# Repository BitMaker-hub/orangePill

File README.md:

# The Orange Pill
## Description
The OrangePill is a new social mechanism to onboard, gift, transfer or sell bitcoin in a physical, safe and reusable way.

It is a real HW Orange Pill that can be used in a community as cash. It also can be the entry point for those who doesn't know anything about Bitcoin and the best, it can be used as many times you want. 

## ATTENTION! This project is still in developement and must be tested on tesnet

## How can I use it?
Receive 💊 ➡️ Create 🌱💦 ➡️ Save ₿ 🔐➡️ Give it away

Receive 🔐 💊 ➡️ Unlock 🌱 ₿ ➡️ Reboot 💊 ➡️ Repeat with others 🔄

## How it works?
### PILL AS A KEYBOARD
The OrangePill works as a input HID device, it emulates keyboard strokes. Every time you push it's button sends keystrokes.
It don't need any specific app to work. Works on any device or pc, you just need to open a notepad or any text editor and press the pill button.

Posible inputs:

- One push:   Shows current status, display options and show xpub or mnemonic depending of it's state.
- Two pushes: Shows # times pill was used, public gpg of interal hw + signed message.
- Hold 5 sec: Depending of it's state > Start seed generation / Unlock seed / Reset pill
- SHAKE: During seed generation or seed unlock.

##PILL STATES

The orangePill has currently three sates.

VIRGIN: No seed present. Needs to generate entropy. 
LOCKED: Seed present. When you make one push you can only see xpub.
UNLOCKED: Seed revealed. When you make one push you can see mnemonic.

## HW Specifictions
- ESP32S2
- LEDs WS2812B
- Button
- Accelerometer KXTJ3-1057
- ATTEC608A

## Libraires
- Main library -> <a href="https://www.arduino.cc/reference/en/libraries/ubitcoin/">uBitcoin</a>
- Adafruit_NeoPixel
- kxtj3-1057
- hidkeyboard

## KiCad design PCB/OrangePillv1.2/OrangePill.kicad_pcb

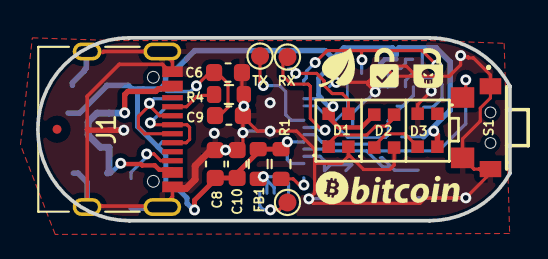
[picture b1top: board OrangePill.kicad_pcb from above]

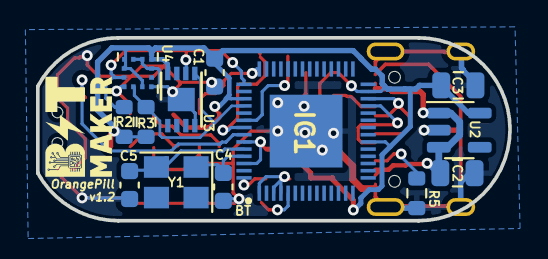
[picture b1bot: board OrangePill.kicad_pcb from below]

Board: 2 copper layers, 26.2 x 10.2 mm, 29 parts (13 on the bottom side), 20 nets.

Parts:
BT1: BOOT; TestPoint_Pad_D1.0mm
C1, C9, C10: 0.1uF; C_0603_1608Metric
C2, C3: 22uF; C_0805_2012Metric
C4, C5: 18pF; C_0603_1608Metric
C6, C8: 1uF; C_0603_1608Metric
D1, D2, D3: WS2812B-2020; WS2812B2020
FB1: 100; R_0603_1608Metric
IC1: ESP32-S2FN4R2; QFN40P700X700X90-57N-D
J1: C2927038; USB_C_Receptacle_XKB_U262-16XN-4BVC11
R1, R2: 10k; R_0603_1608Metric
R3: 10K; R_0603_1608Metric
R4, R5: 5.1k; R_0603_1608Metric
RX1: RX; TestPoint_Pad_D1.0mm
S1: TS24CA
TX1: TX; TestPoint_Pad_D1.0mm
U2: AP2112K-3.3; SOT-23-5
U3: ATECC608A-MAHDA; DFN-8-1EP_3x2mm_P0.5mm_EP1.3x1.5mm
U4: KXTJ3-1057; Kionix_LGA-12_2x2mm_P0.5mm_LayoutBorder2x4y
Y1: 40MHz; Crystal_SMD_3225-4Pin_3.2x2.5mm
fiducial: Fiducial_0.5mm_Mask1.5mm

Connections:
+3V3: C1.1, C3.1, C6.1, C8.1, C9.1, C10.1, D1.4 (VDD), D2.4 (VDD), D3.4 (VDD), FB1.2, IC1.20 (VDD3P3_RTC), IC1.27 (VDD3P3_RTC_IO), IC1.45 (VDD3P3_CPU), IC1.51 (VDDA_2), IC1.54 (VDDA_3), R1.1, R2.2, R3.2, U2.5 (VOUT), U3.8 (VCC), U4.3 (IO_VDD), U4.7 (VDD), U4.10 (VDD), U4.11 (IO_VDD)
+5V: C2.1, J1.A4 (VBUS), J1.A9 (VBUS), J1.B4 (VBUS), J1.B9 (VBUS), U2.1 (VIN), U2.3 (EN)
/D+: IC1.25 (GPIO19), J1.A6 (D+), J1.B6 (D+)
/D-: IC1.26 (GPIO20), J1.A7 (D-), J1.B7 (D-)
/LED: D1.3 (DI), IC1.42 (GPIO38)
/PSH1: IC1.50 (GPIO45), S1.3 (COM)
/RESET: IC1.56 (CHIP_PU), R1.2
/SCL: IC1.43 (MTCK), R2.1, U3.6 (SCL), U4.12 (SCL)
/SDA: IC1.46 (MTDI), R3.1, U3.5 (SDA), U4.2 (SDA)
GND: C1.2, C2.2, C3.2, C4.1, C5.1, C6.2, C8.2, C9.2, C10.2, D1.2 (GND), D2.2 (GND), D3.2 (GND), IC1.57 (EP), J1.A1 (GND), J1.A12 (GND), J1.B1 (GND), J1.B12 (GND), J1.S1 (SHIELD), R4.2, R5.2, S1.1, S1.2, S1.4 (NO), U2.2 (GND), U3.4 (GND), U3.9 (EP), U4.1 (ADDR), U4.4 (RES), U4.6 (GND), U4.8 (GND), U4.9 (GND)
unnamed: BT1.1, IC1.5 (GPIO0)
unnamed: C4.2, IC1.53 (XTAL_P), Y1.1
unnamed: C5.2, IC1.52 (XTAL_N), Y1.2
unnamed: D1.1 (DO), D2.3 (DI)
unnamed: D2.1 (DO), D3.3 (DI)
unnamed: FB1.1, IC1.1 (VDDA_1), IC1.3 (VDD3P3_1), IC1.4 (VDD3P3_2)
unnamed: IC1.48 (U0TXD), TX1.1
unnamed: IC1.49 (U0RXD), RX1.1
unnamed: J1.A5 (CC1), R4.1
unnamed: J1.B5 (CC2), R5.1

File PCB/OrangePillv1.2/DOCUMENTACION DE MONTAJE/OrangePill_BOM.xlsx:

Comments | Designator | Footprint | JLCPCB Part #
WS2812B-2020 | D2,D1,D3 | 2.0x2.0mm | C965555
 | FB1 | IND-SMD | C14709
 | J1 | USB-C | C2927038
1uF | C6,C8 | C0603 | C105504
10k | R1,R2 | R0603 | C25804
16V 100nF | C9,C10,C1 | C0603 | C1853791
5.1k | R4,R5 | R0603 | C23186
TS24CA | S1 | SMD | C393942
X322540MPB4SI | Y1 | Crystal_SMD_3225-4Pin_3.2x2.5mm | C9010
ATECC608A-MAHDA | U3 | DFN-8-1EP_3x2mm_P0.5mm_EP1.3x1.5mm | ATECC608A-MAHDA
KXTJ3-1057 | U4 | Kionix_LGA-12_2x2mm_P0.5mm_LayoutBorder2x4y | C442603
18pF 50V | C5,C4 | C0603 | C107040
10K | R3 | R0603 | C25804
22uF 25V | C2,C3 | C_0805_2012Metric | C602037
ESP32-S2FN4R2 | IC1 | QFN40P700X700X90-57N-D | C2844252
AP7365-33WG-7 | U2 | SOT-23-5 | C150742

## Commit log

2022-10-27 First commit initial tests
2022-10-27 Joined accelerometer tests
    - TODO properly give fucntionality before adding ATTEC
2022-11-06 Major Pill changes
    - Code structure
    - Moving out gerbers
    - Added all logic of pill
    - Added accelerometer work
    - Added button work
    - Added led effects
2022-11-17 OrangePill v0.1
    - Added uBitcoin library
    - Added mnemonic generation
    - Added xpuv generation
    - Added Readme
    - Added License
2022-11-22 Adding uBitcoin functions
    [OK] - Generate seed
    [OK] - Show xpub
    [OK] - Show seed words
    [OK] - Save it in EEPROM
    [OK] - Get seed from EEPROM
    TODO:
